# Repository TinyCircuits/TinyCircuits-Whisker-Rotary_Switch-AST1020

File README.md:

# TinyCircuits Wireling Rotary Switch
# AST1020 Rev3

The design files are located under design_files/ for the TinyCircuits AST1020 Rev 3 PCB. This is a Wireling board which features a 10-position Rotary Switch. The on-board SX1505 I2C expander is used with the SH7010 library to send back the position over I2C.

Format is in Cadsoft Eagle format - Eagle version 6.2 was used for the original design.

For more infomation on this, check out the product page at TinyCircuits.com

# License:

Design by TinyCircuits.
All design files are released under the Creative Commons Attribution Share-Alike 3.0 License, see the following link for details: http://creativecommons.org/licenses/by-sa/3.0

All text above must be included in any redistribution or derived design

This project uses designs and concepts developed as part of the Arduino project and the LilyPad project.  The TinyCircuits design files themselves (schematics, PCB and libraries) are not directly derived from these works' design files and have been created new, however the concepts and basic architecture behind the TinyDuino and TinyLily products are derived and we thank the hard work of the organizations below for their contributions to open-source hardware:
  
Original Arduino Uno Design by Team Arduino

LilyPad Arduino Design by Leah Buechley and Sparkfun Electronics

Please support the open-source hardware community

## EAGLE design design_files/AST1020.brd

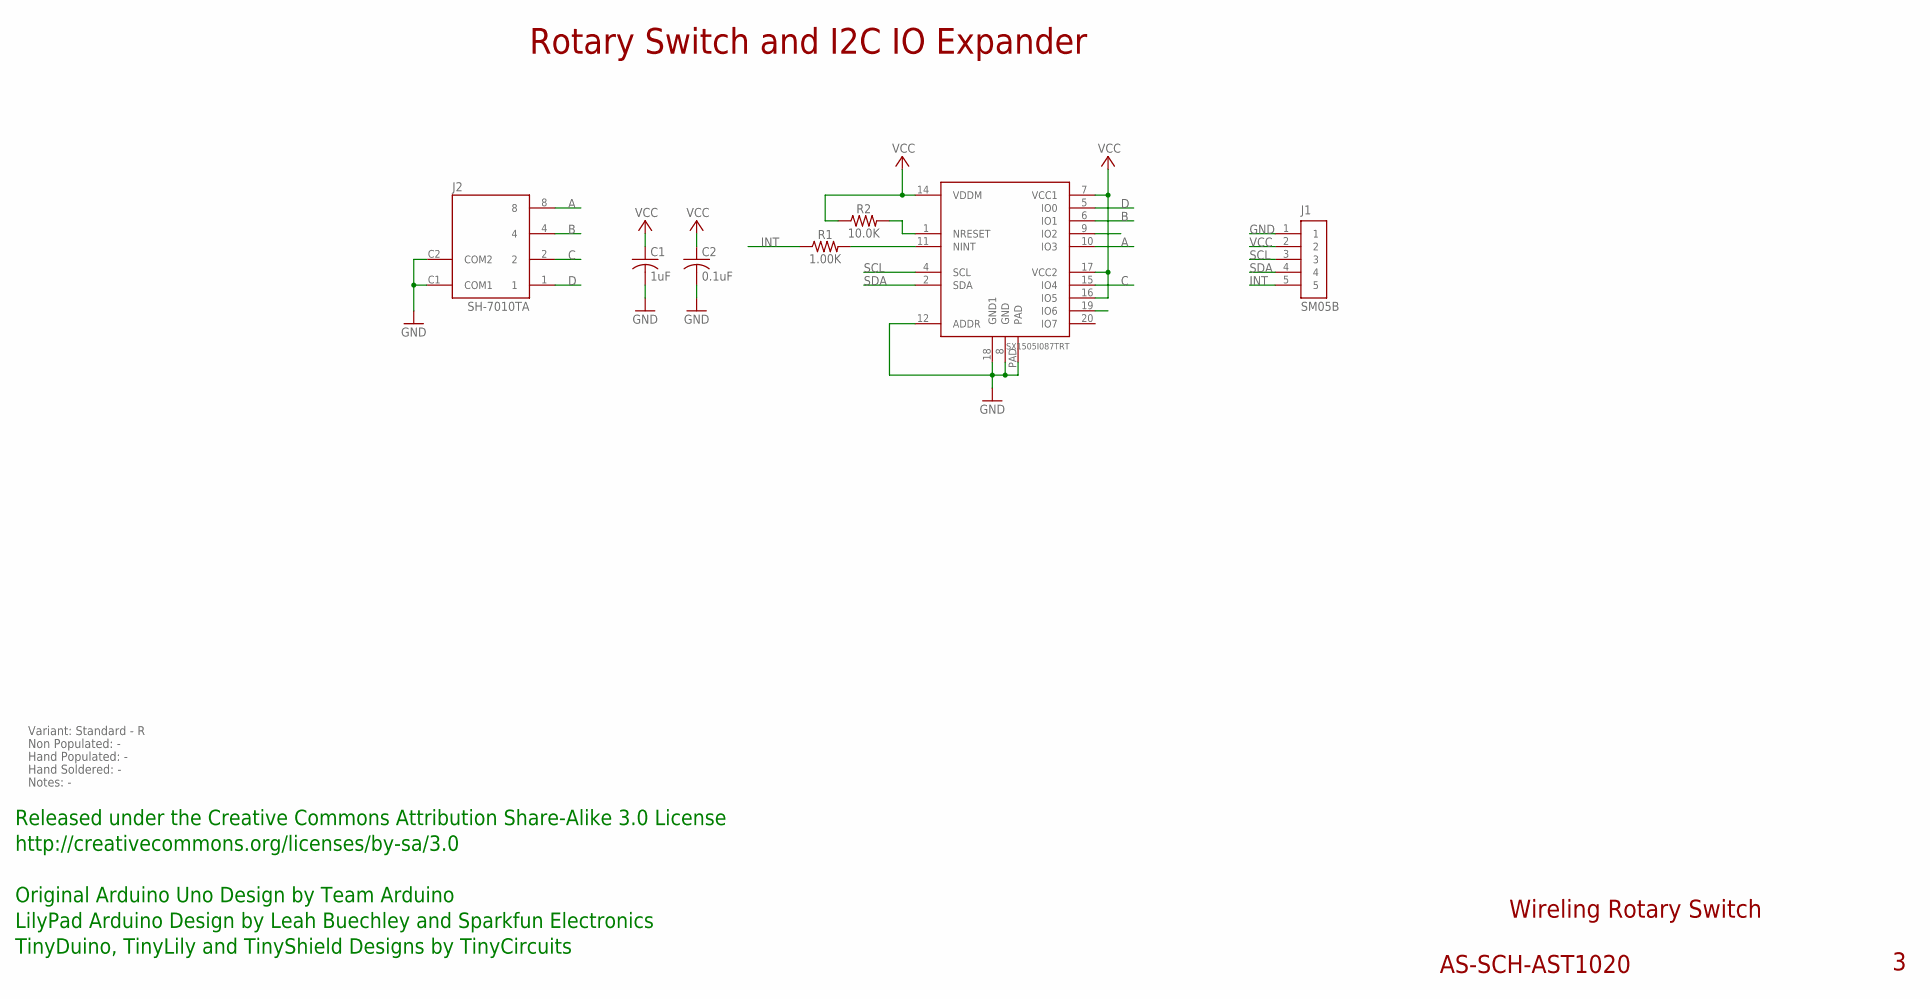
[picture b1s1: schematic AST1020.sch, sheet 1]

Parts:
C1: 1uF; C0402; PARTNO AS-ITM-00105
C2: 0.1uF; C0402
J1: SM05B; JST_SH_5X1_EDGE
J2: SH-7010TA; SH-7000
R1: 1.00K; 0402
R2: 10.0K; 0402
U1: SX1505I087TRT; QFN-UT20

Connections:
A: J2.8, U1.10 (IO3)
B: J2.4, U1.6 (IO1)
C: J2.2, U1.15 (IO4)
D: J2.1, U1.5 (IO0)
GND: C1.2, C2.2, J1.1, J2.C1 (COM1), J2.C2 (COM2), U1.8 (GND), U1.12 (ADDR), U1.18 (GND1), U1.PAD
INT: J1.5, R1.1
unnamed: R1.2, U1.11 (NINT)
unnamed: R2.2, U1.1 (NRESET)
SCL: J1.3, U1.4 (SCL)
SDA: J1.4, U1.2 (SDA)
VCC: C1.1, C2.1, J1.2, R2.1, U1.7 (VCC1), U1.14 (VDDM), U1.16 (IO5), U1.17 (VCC2)

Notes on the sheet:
Wireling Rotary Switch
AS-SCH-AST1020
Rotary Switch and I2C IO Expander
Released under the Creative Commons Attribution Share-Alike 3.0 License
http://creativecommons.org/licenses/by-sa/3.0
Original Arduino Uno Design by Team Arduino
TinyDuino, TinyLily and TinyShield Designs by TinyCircuits
LilyPad Arduino Design by Leah Buechley and Sparkfun Electronics
Non Populated: -
Hand Populated: -
Hand Soldered: -
Variant: Standard - R
Notes: -

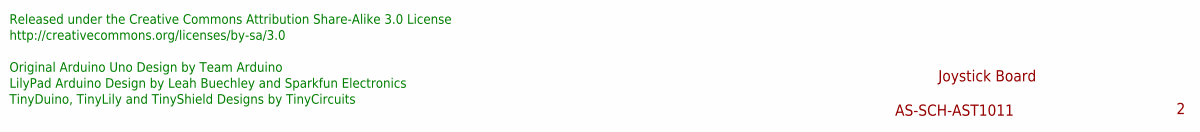
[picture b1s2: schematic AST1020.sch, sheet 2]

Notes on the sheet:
Joystick Board
AS-SCH-AST1011
Released under the Creative Commons Attribution Share-Alike 3.0 License
http://creativecommons.org/licenses/by-sa/3.0
Original Arduino Uno Design by Team Arduino
TinyDuino, TinyLily and TinyShield Designs by TinyCircuits
LilyPad Arduino Design by Leah Buechley and Sparkfun Electronics

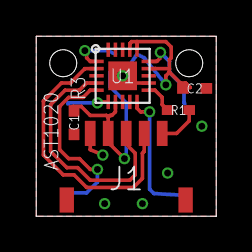
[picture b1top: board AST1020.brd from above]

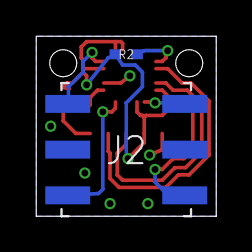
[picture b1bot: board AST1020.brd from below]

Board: 2 copper layers, 10.0 x 10.0 mm, 8 parts (2 on the bottom side), 11 nets.

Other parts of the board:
U$1: DOCFIELD-TINYCIRCUITS-PCB

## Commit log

2019-07-17 added images
2019-07-18 updated code to use Port 0
2019-07-30 updated to use Port 0
2019-08-02 added datasheet
2019-12-17 updated documentation
2020-01-02 updated library and example
2020-01-02 updated sketch
2020-02-04 mass image update
2020-02-06 added libraries to example folder
2020-02-07 image update
2020-02-17 remove
2020-02-17 datasheet
2020-02-18 fix program
2020-02-18 kill library
2020-03-09 updated program
2020-08-14 Add CAD data
